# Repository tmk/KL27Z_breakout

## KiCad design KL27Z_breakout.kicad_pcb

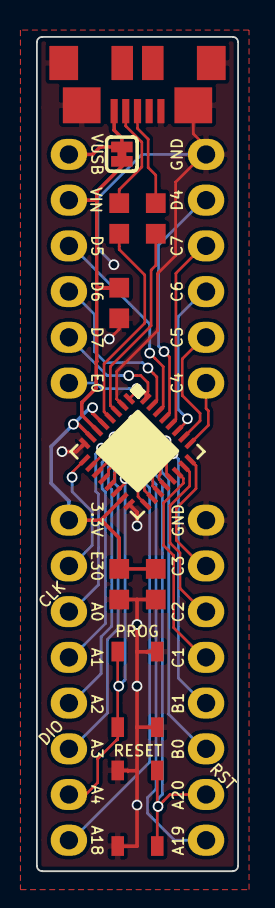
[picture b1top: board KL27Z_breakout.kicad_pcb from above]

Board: 2 copper layers, 11.2 x 46.4 mm, 14 parts (0 on the bottom side), 31 nets.

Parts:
C1: 4.7u; C_1608
C2: 2.2u; C_1608
C4: 0.1u; C_1608
J1: USB_mini_micro_B; USB_microB
P1, P4: CONN_01X06; Pin_Header_Straight_1x06
P2, P3: CONN_01X08; Pin_Header_Straight_1x08
R1, R2: 33; R_1608
SJ1: SOLDER_JUMPER; SOLDER_JUMPER_2_WIRED
SW1, SW2: SW_PUSH; SW_ALPS_SKRP
U1: MKL27Z256VFM4; QFN-32-1EP_5x5mm_Pitch0.5mm

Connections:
+3V3: C2.1, C4.1, P2.1, U1.5, U1.7, U1.15
GND: C1.2, C2.2, C4.2, J1.5, J1.6, P3.8, P4.6, SW1.2, SW2.2, U1.2, U1.8, U1.16
unnamed: J1.2, R2.2
unnamed: J1.3, R1.2
unnamed: R1.1, U1.3
unnamed: R2.1, U1.4
PTA0: P2.3, U1.10
PTA1: P2.4, U1.11
PTA2: P2.5, U1.12
PTA3: P2.6, U1.13
PTA4: P2.7, SW2.1, U1.14
PTA18: P2.8, U1.17
PTA19: P3.1, U1.18
PTA20: P3.2, SW1.1, U1.19
PTB0: P3.3, U1.20
PTB1: P3.4, U1.21
PTC1: P3.5, U1.22
PTC2: P3.6, U1.23
PTC3: P3.7, U1.24
PTC4: P4.1, U1.25
PTC5: P4.2, U1.26
PTC6: P4.3, U1.27
PTC7: P4.4, U1.28
PTD4: P4.5, U1.29
PTD5: P1.3, U1.30
PTD6: P1.4, U1.31
PTD7: P1.5, U1.32
PTE0: P1.6, U1.1
PTE30: P2.2, U1.9
VBUS: J1.1, P1.1, SJ1.1
VREGIN: C1.1, P1.2, SJ1.2, U1.6

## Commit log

2016-06-09 Add files
2016-07-09 Save some works
2016-07-10 400mil pcb
2016-07-10 Save 300mil work
2016-07-11 Route traces for 300mil PCB
2016-07-11 Add silk screen fill under thermal pad
2016-08-01 Fix D- and D+ lines and pin header position
2016-08-01 Shorten board size
2016-09-21 Add schematic
